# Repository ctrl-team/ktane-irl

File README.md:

# ktane-irl

## Overview
This project is a real-life adaptation of the game "Keep Talking and Nobody Explodes.".
Modules may use Arduino or different microcontrollers, with each module documented in its own directory.

## Features
* Real-life bomb-defusal gameplay
* Advanced component system

## Software Requirements
- Arduino IDE
- TFT_eSPI library (included in lib/)

## Installation

### 1. Clone the Repository
```sh
git clone https://github.com/ctrl-team/ktane-irl.git
cd ktane-irl
```
### 2. Configure TFT_eSPI
TFT_eSPI requires a proper `User_Setup_Select.h` configuration. Users must manually edit:
```sh
TFT_eSPI/User_Setup_Select.h
```
#### to include:
for main timer board
```cpp
#include "User_Setups/Setup304_RP2040_ILI9341_Waveshare_2_4"
```
for button module
```cpp
#include <User_Setups/Setup305_RP2040_GC9A01.h>
```

## License
This project is licensed under GNU General Public License v3.0. See the LICENSE file for details.

## Acknowledgments
- [TFT_eSPI by Bodmer](https://github.com/Bodmer/TFT_eSPI)
- [RPI Pico Schematic and footprint by ncarandini](https://github.com/ncarandini/KiCad-RP-Pico)

## Contributing
Feel free to submit pull requests or open issues for bug reports and feature requests.

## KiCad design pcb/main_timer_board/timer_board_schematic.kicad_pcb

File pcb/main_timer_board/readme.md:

# Main Timer Module PCB

KiCad project for the Main Timer Module in a KTANE replica.

Raspberry Pi symbol & footprint sourced from [here](https://github.com/ncarandini/KiCad-RP-Pico).

# Files

📜 timer_board_schematic.kicad_sch - Schematic

🖼️ timer_board_schematic.kicad_pcb - PCB Layout

⚙️ timer_board_schematic.kicad_pro - Project Settings

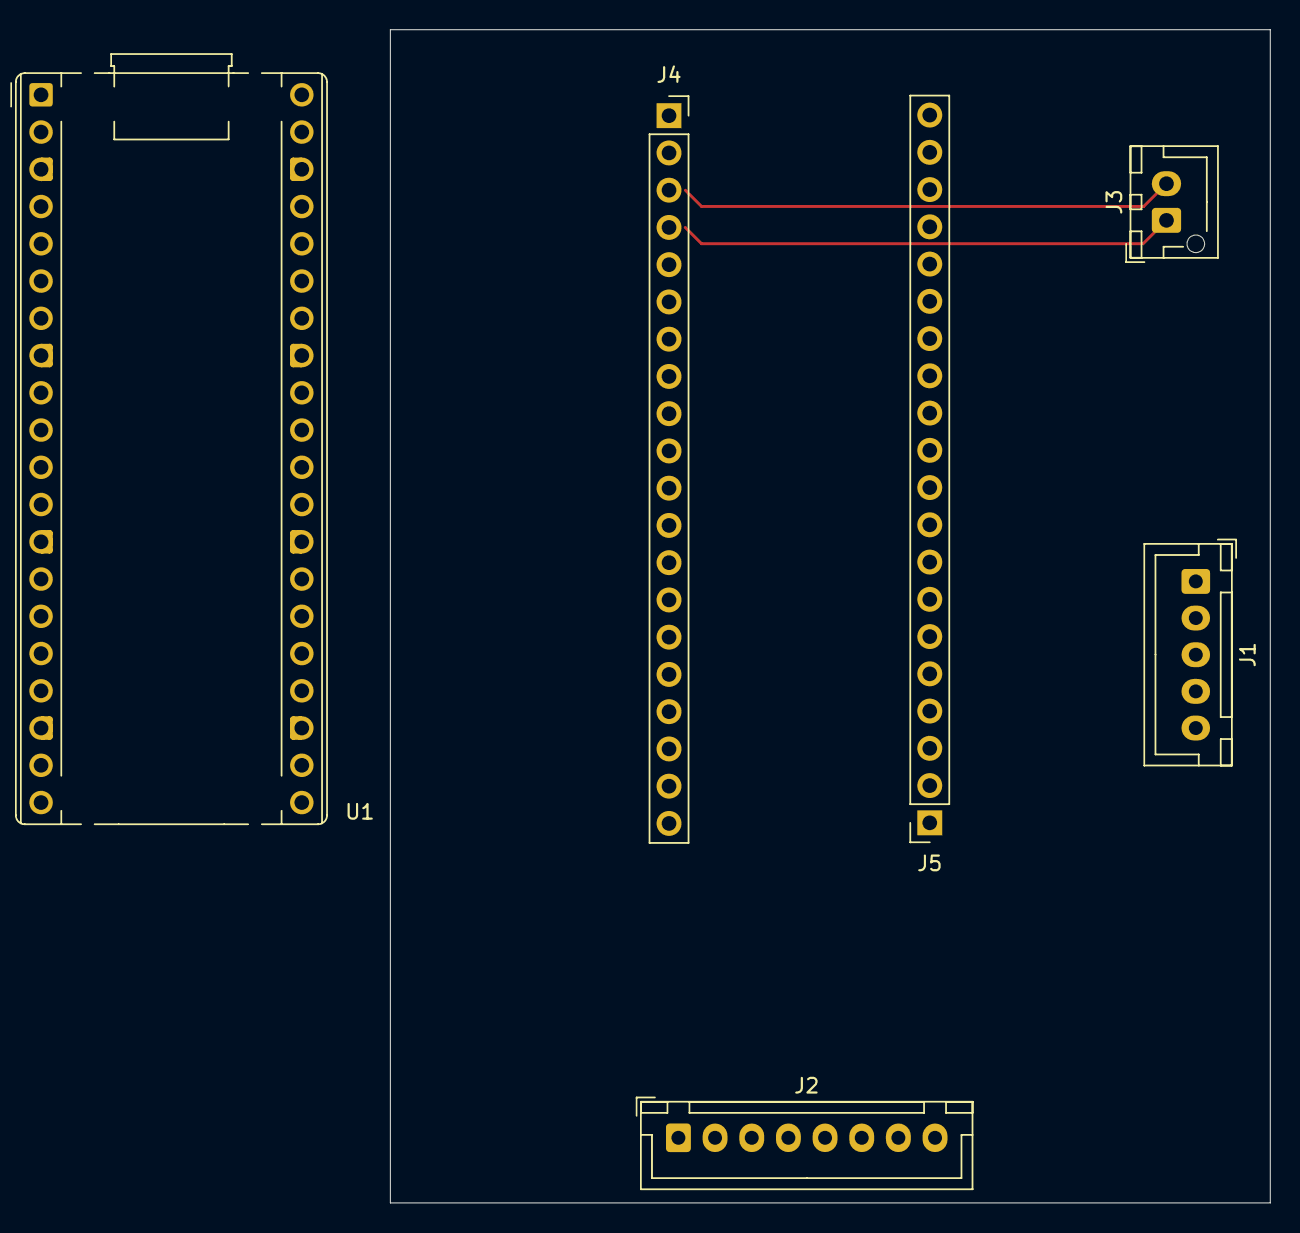
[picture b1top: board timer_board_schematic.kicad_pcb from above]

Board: 2 copper layers, 60.0 x 80.0 mm, 6 parts (0 on the bottom side), 14 nets.

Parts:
J1: Buttons Socket; JST_XH_B5B-XH-A_1x05_P2.50mm_Vertical
J2: Screen Socket; JST_XH_B8B-XH-A_1x08_P2.50mm_Vertical
J3: Buzzer Socket; JST_XH_B2B-XH-AM_1x02_P2.50mm_Vertical
J4, J5: Conn_01x20_Socket; PinSocket_1x20_P2.54mm_Vertical
U1: Pico; RaspberryPi_Pico_Common_THT

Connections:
unnamed: J1.1, J5.7
unnamed: J1.2, J5.6
unnamed: J1.3, J5.5
unnamed: J1.4, J5.4
unnamed: J1.5, J5.3
unnamed: J2.1, J2.8, J5.16
unnamed: J2.2, J4.16
unnamed: J2.3, J4.11
unnamed: J2.4, J4.12
unnamed: J2.5, J4.14
unnamed: J2.6, J4.15
unnamed: J2.7, J5.18
unnamed: J3.1, J4.4
unnamed: J3.2, J4.3

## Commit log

2025-02-13 Use new display driver
2025-02-13 Add README.md to main_timer_board
2025-02-13 Fix button double-clicking, implement buzzer effects
2025-02-13 Little changes
2025-02-14 fix negative time and rotate screen
2025-02-14 Enlarge content font size
2025-02-14 Enlarge game over screen font
2025-02-14 UP BUTTON
    bug: when "start game" is selected, and up button is pressed, the selection wont skip to "information"
2025-02-14 up button working
2025-02-15 Update README.md
    Diagram, and button pins
2025-02-15 Fix buttons
2025-02-16 test controller and board - i2c bus
2025-02-16 fixed invalid handling of requests
2025-02-16 quick fix
2025-02-16 try again
2025-02-16 Add timeout handling for I2C communication
    - Implemented a 80ms timeout in `receive_byte()` to prevent infinite waiting if a module does not respond.
    - Added error detection in `send_request()` to log failed transmissions.
    - Introduced a small delay in `initialize_devices()` to reduce I2C bus congestion.
    - Improved overall stability and reliability of module detection.
2025-02-16 Add logging
2025-02-16 Implement send_request with 2 byte data
2025-02-16 debug module
2025-02-16 count streak
2025-02-17 implement packet broadcast, broadcast timer to modules
2025-02-17 refresh modules states more often
2025-02-17 Rewrite UNKNOWN to use uint8_t
2025-02-17 Add readme
2025-02-17 add RGB diode
2025-02-18 main timer board pcb files
2025-02-18 streak sound
2025-02-18 gitignore kicad lock files
2025-02-19 detecting press and hold of a button
2025-02-19 Basic button logic
2025-02-20 Bug fixes
    - Fixed the timer digit checking:
    Checks tens and ones digits for both minutes and seconds
    For example, will now correctly detect "4" in times like 4:51, 1:40, 0:14
    - Fixed the press/hold logic:
    For cases that require immediate press (like batteries + FRK), now strictly checks that the duration was less than HOLD_TIME
    Gives strike if holding when should press immediately
2025-02-20 Implement module functionality
2025-02-20 Add module to bus_controller.h, fix typo
2025-02-20 replace tabs with spaces
2025-02-20 Replace streak with strike oops
2025-02-20 Restore removed game logic (by mistake)
2025-02-20 Major changes
    - refactor to snakeCase
    - implement `0x1` command for updating module state
    - fix typo in `UNKOWN_STATE` -> `UNKNOWN_STATE`
    - fix few mistakes in `button_module` such as missing `static_cast`
2025-02-20 game off by start
2025-02-20 broadcast playing packet after unpausing
2025-02-20 implement i2c_receiver
2025-02-21 Few bux fixes - Implement checking if BUS device is available - Fixed unfinished IF statement - broadcast NOT_STARTED by default - Fixed game over menu
2025-02-22 Create buis_receiver and task_scheduler
2025-02-22 Remove i2c_receiver
2025-02-22 Restructurize code
2025-02-27 small refactor
2025-02-28 game-winning mechanics
2025-02-28 Small fix
2025-02-28 Implement serial number, flags and ports
2025-02-28 Use FRK from bus
2025-02-28 Add randomization and display settings for batteries, flags, and ports
2025-02-28 Refactor configuration handling to use 'config' instead of 'configuration' and add batteries support
2025-02-28 Add `justStarted` flag to BusReceiver and update button randomization logic
2025-03-01 fix repeated clicks
2025-03-22 Driver for button module's round display
2025-03-22 Button screen driver
